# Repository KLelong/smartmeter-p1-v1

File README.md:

# smartmeter-p1-v1
Readout of a Flemish smartmeter via the P1 port and publish it to MQTT.
The meter uses the DSMR v5 protocol, so probably recent Dutch meters can be read out.

## Software

The software is intended to run on an ESP8266 device.
This version is made with the Arduino IDE.
The software is based on https://github.com/neographikal/P1-Meter-ESP8266-MQTT and others.

## Hardware

I made a motherboard containing a Wemos D1 mini R2 and the hardware to connect to the P1 port of the energy-meter. Later I swapped the mini R2 with a mini Pro, because the poor WiFi signal at my meter. So both can be used.

## Risk

Both software and hardware are running fine at my home. Using any of this is at your own risk.

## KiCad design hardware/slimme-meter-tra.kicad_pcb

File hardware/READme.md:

The board is setup to be it's own housing.

The first prototype, so the board was not cleaned after soldering.

The device in action on the meter.
There is a lid, but the hole for the LED is not aligned. 
Also I didn't mount the switch because I didn't have a suitable type.
That switch is there to reset the device to "factory seetings".

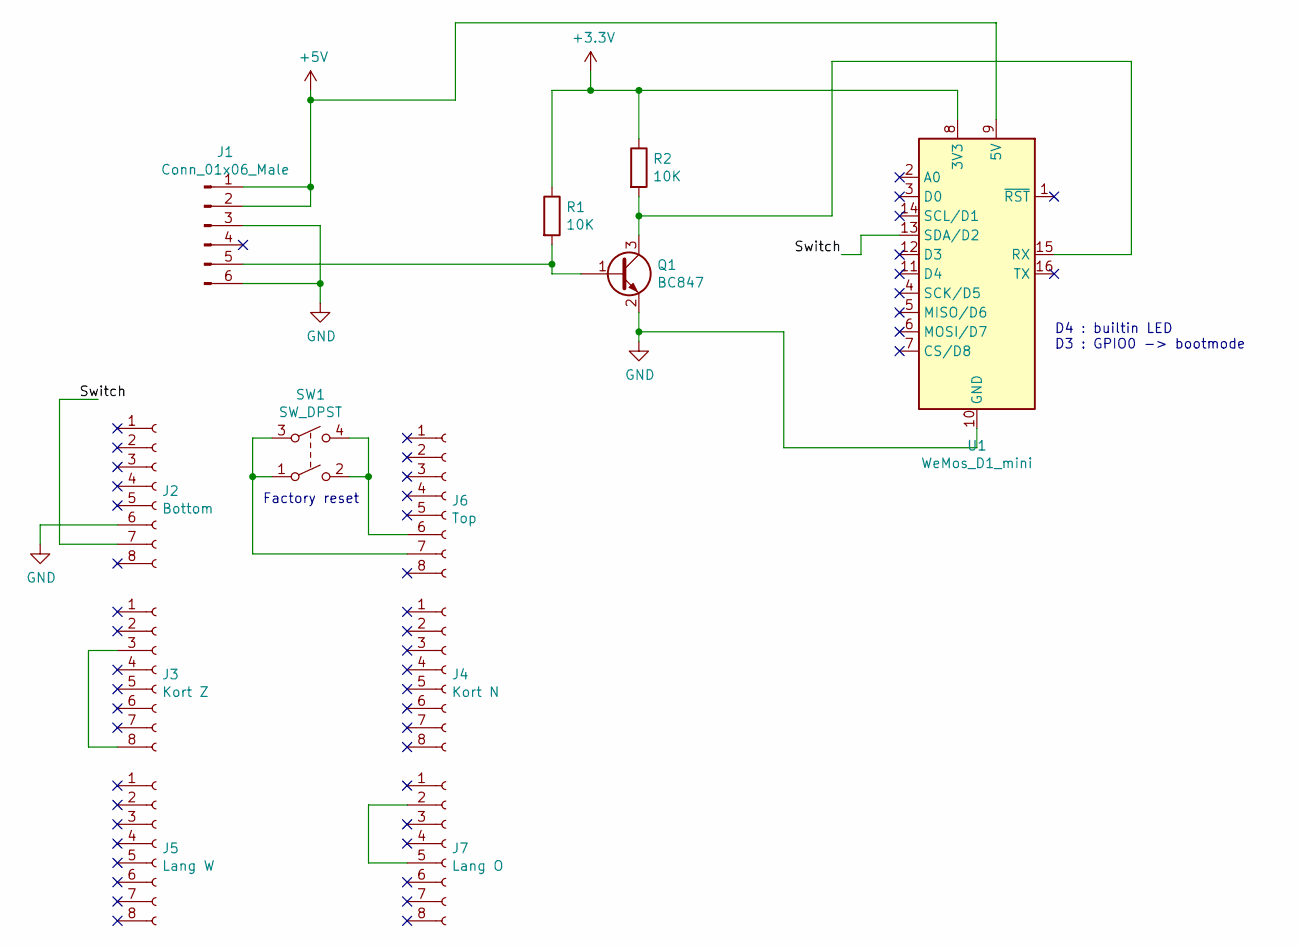
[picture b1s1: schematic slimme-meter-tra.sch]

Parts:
J1: Conn_01x06_Male; PinHeader_1x06_P2.54mm_Vertical_SMD_Pin1Right
J2: Bottom; bottom
J3: Kort Z; zij-kort
J4: Kort N; zij-lang
J5: Lang W; zij-kort
J6: Top; top
J7: Lang O; zij-lang
Q1: BC847; SOT-23
R1, R2: 10K; R_0805_2012Metric_Pad1.15x1.40mm_HandSolder
SW1: SW_DPST; SW_Push_2P2T_Vertical_E-Switch_800UDP8P1A1M6
U1: WeMos_D1_mini; wemos-mini-d1-SMT

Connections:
+3V3: R1.1, R2.1, U1.8 (3V3)
+5V: J1.1, J1.2, U1.9 (5V)
/Switch: J2.7, U1.13 (SDA/D2)
GND: J1.3, J1.6, J2.6, Q1.2 (E), U1.10 (GND)
unnamed: J1.5, Q1.1 (B), R1.2
unnamed: J3.3, J3.8
unnamed: J6.6, SW1.2, SW1.4
unnamed: J6.7, SW1.1, SW1.3
unnamed: J7.2, J7.5
unnamed: Q1.3 (C), R2.2, U1.15 (RX)

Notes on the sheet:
D4 : builtin LED D3 : GPIO0 -> bootmode
Factory reset

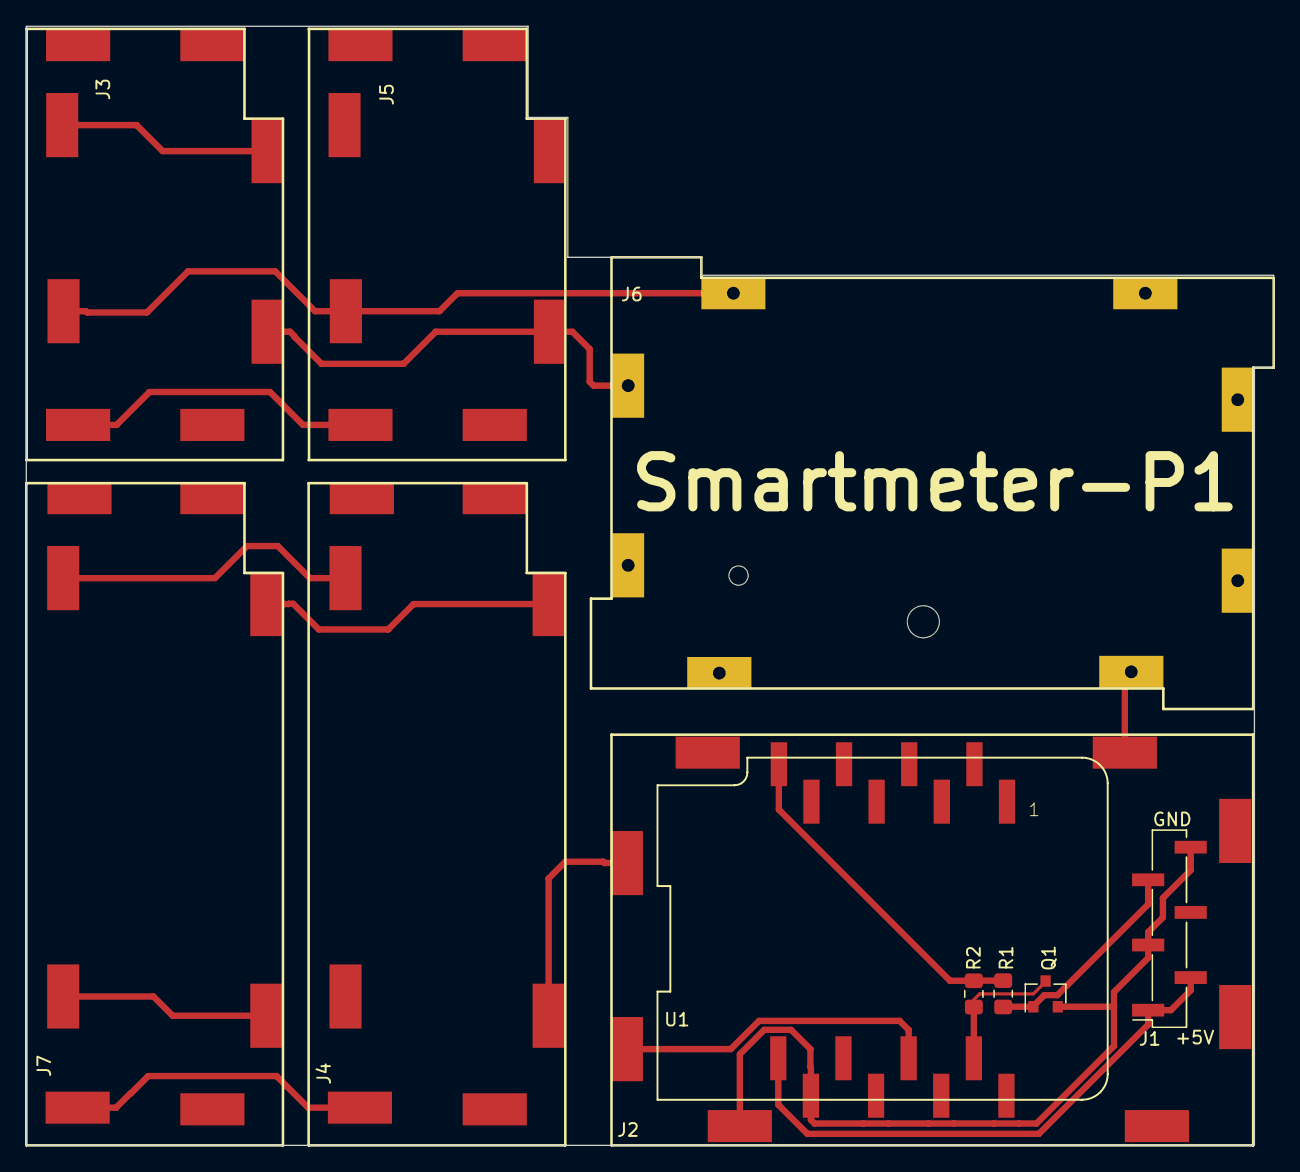
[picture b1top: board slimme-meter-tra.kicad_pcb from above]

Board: 2 copper layers, 97.2 x 87.2 mm, 11 parts (0 on the bottom side), 8 nets.

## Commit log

2021-06-21 Initial hardware
2021-06-21 Initial software
2021-06-21 Rename READ.md to READme.md
2021-06-21 Removed OTA data
2021-06-21 Update READme.md
    added some information
2021-06-21 Update README.md
    corrected type
2021-06-21 Documentation updates to hardware
